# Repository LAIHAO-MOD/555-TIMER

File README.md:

# 555-TIMER

Functional transistor-scale replica of classic NE555 timer .

Use KICAD 5.1 as Schematic & Pcb design software .

Production Gerber files included .

layout

3d rendering

pcb

assembled

testing wavefome

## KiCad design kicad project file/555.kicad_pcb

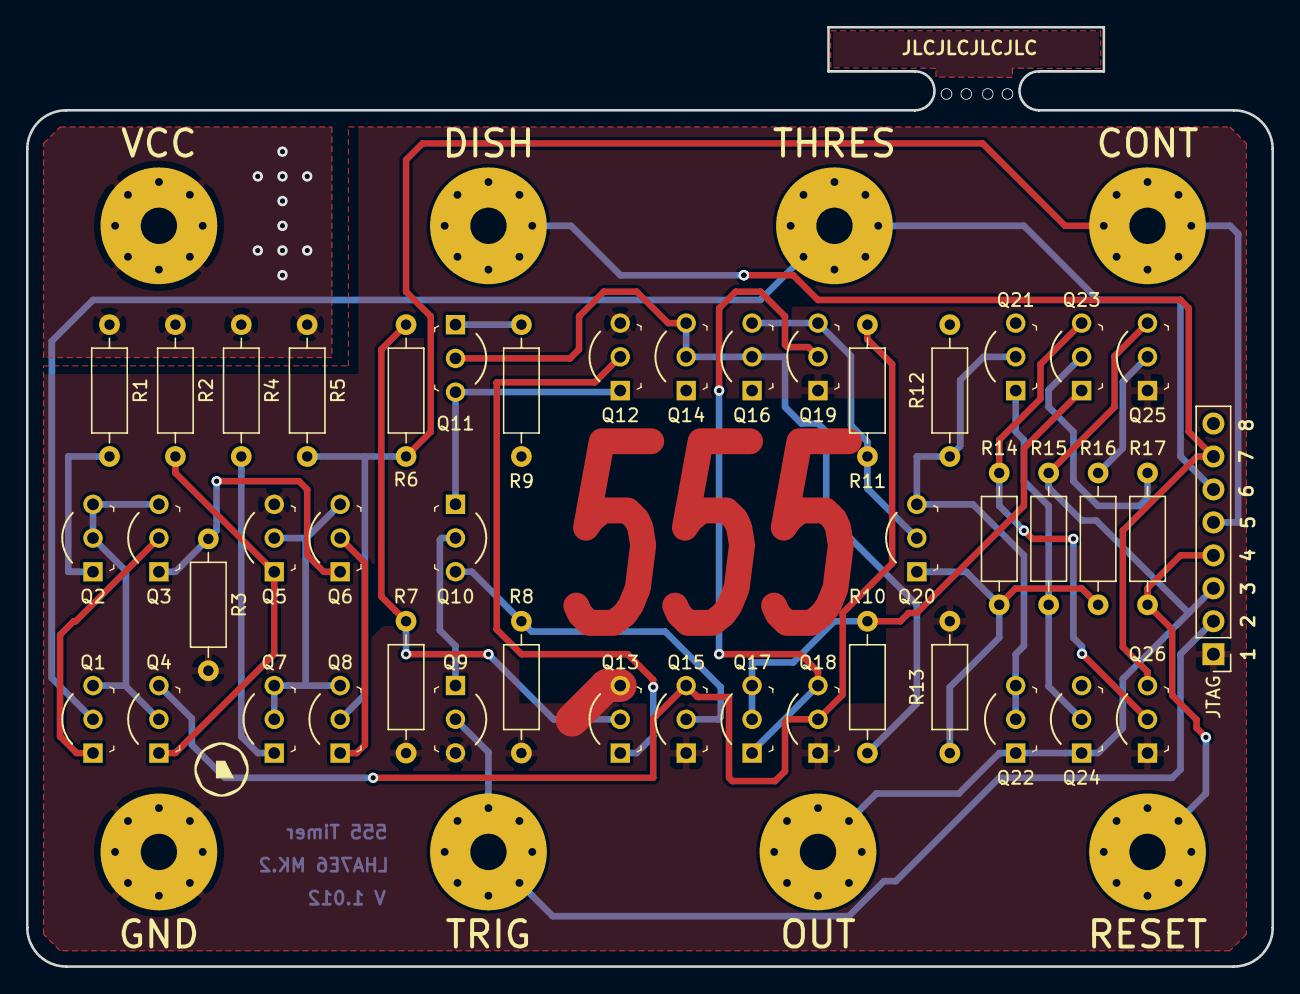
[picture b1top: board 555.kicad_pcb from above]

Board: 2 copper layers, 96.0 x 72.4 mm, 52 parts (0 on the bottom side), 33 nets.

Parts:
CONT: Control voltage; MountingHole_4.5mm_Pad_Via
DISH: Discharge; MountingHole_4.5mm_Pad_Via
GND: GND; MountingHole_4.5mm_Pad_Via
JTAG: jtag; PinHeader_1x08_P2.54mm_Vertical
OUT: Output; MountingHole_4.5mm_Pad_Via
Q1, Q3, Q6, Q8, Q15, Q17, Q18, Q19, Q20, Q21, Q24, Q25, Q26: 2N3904; TO-92-3_Formed_Leads
Q2, Q4, Q5, Q7, Q9, Q10, Q11, Q12, Q13, Q14, Q16, Q22, Q23: 2N3906; TO-92-3_Formed_Leads
R1, R4, R5, R11, R13: 4.7K; R_Axial_DIN0207_L6.3mm_D2.5mm_P10.16mm_Horizontal
R2: 820; R_Axial_DIN0207_L6.3mm_D2.5mm_P10.16mm_Horizontal
R3: 10K; R_Axial_DIN0207_L6.3mm_D2.5mm_P10.16mm_Horizontal
R6, R7: 4.7k; R_Axial_DIN0207_L6.3mm_D2.5mm_P10.16mm_Horizontal
R8, R17: 100K; R_Axial_DIN0207_L6.3mm_D2.5mm_P10.16mm_Horizontal
R9: 1K; R_Axial_DIN0207_L6.3mm_D2.5mm_P10.16mm_Horizontal
R10: 15K; R_Axial_DIN0207_L6.3mm_D2.5mm_P10.16mm_Horizontal
R12: 6.8K; R_Axial_DIN0207_L6.3mm_D2.5mm_P10.16mm_Horizontal
R14: 100; R_Axial_DIN0207_L6.3mm_D2.5mm_P10.16mm_Horizontal
R15: 3.9K; R_Axial_DIN0207_L6.3mm_D2.5mm_P10.16mm_Horizontal
R16: 220; R_Axial_DIN0207_L6.3mm_D2.5mm_P10.16mm_Horizontal
RESET: Reset; MountingHole_4.5mm_Pad_Via
THRES: Threshold; MountingHole_4.5mm_Pad_Via
TRIG: Trigger; MountingHole_4.5mm_Pad_Via
VCC: VCC; MountingHole_4.5mm_Pad_Via

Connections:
unnamed: Q1.1, Q3.2
unnamed: Q1.3, Q2.2, Q2.3, Q3.3, Q4.2
unnamed: Q2.1, R1.2
unnamed: Q3.1, Q6.1, R3.1
unnamed: Q4.1, Q5.1, R2.2
unnamed: Q5.2, Q6.3, Q7.2, Q7.3, Q8.3
unnamed: Q6.2, Q8.1
unnamed: Q7.1, R4.2
unnamed: Q10.1, Q11.3, Q12.1
unnamed: Q9.1, Q10.2
unnamed: Q10.3, Q15.2, R8.1
unnamed: Q11.1, R9.2
unnamed: Q11.2, Q14.2, Q14.3, Q16.2, R10.1
unnamed: Q12.2, Q13.1
unnamed: Q13.2, R6.2, R7.1
unnamed: Q4.3, Q15.3, Q18.2, R11.2
unnamed: Q16.3, Q19.3, Q20.2, R11.1
unnamed: Q17.1, Q18.3, Q19.2
unnamed: Q17.2, Q17.3, Q23.1, R10.2
unnamed: Q20.1, R13.1, R14.1, R16.2
unnamed: Q20.3, Q21.2, Q22.2, Q22.3, R12.2
unnamed: Q21.1, Q24.2, R15.1
unnamed: Q23.2, R17.2
unnamed: Q23.3, Q26.2, R14.2
unnamed: Q25.2, R16.1
Threshold: JTAG.6, Q1.2, THRES.1
controlvoltage: CONT.1, JTAG.5, Q8.2, R5.2, R6.1
discharge: DISH.1, JTAG.7, Q26.3
gnd: GND.1, JTAG.1, Q5.3, Q9.3, Q12.3, Q13.3, Q15.1, Q18.1, Q19.1, Q25.1, Q26.1, R3.2, R7.2, R8.2, R13.2
output: JTAG.3, OUT.1, Q22.1, Q24.1, Q25.3, R15.2
reset: JTAG.4, R17.1, RESET.1
trigger: JTAG.2, Q9.2, TRIG.1
vcc: JTAG.8, Q14.1, Q16.1, Q21.3, Q24.3, R1.1, R2.1, R4.1, R5.1, R9.1, R12.1, VCC.1

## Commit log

2019-12-30 Create 1
